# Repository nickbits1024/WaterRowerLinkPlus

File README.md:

# WaterRower Link+

## Description
WaterRower Link+ is a bluetooth module designed for any WaterRower with the S4 monitor.  It provides all the functionality of the official WaterRower ComModule as well as many additional features.

## Features
- Replaces WaterRower ComModule and External ANT+ Module
  - External ANT+ connection Works on M1 when using recommended cable (unlike the official ANT+ Plugin-In module!)
- Bluetooth
  - Bluetooth Fitness Machine Profile
    - Rower Data
    - Indoor Bike Data
  - Supports BLE HRMs
- ANT+
  - Fitness Equipment Profile
  - Supports ANT+ HRMs
- S4 monitor heart rate provider
  - Sends captured ANT+/BLE HR data for display on S4 monitor
- ANT+ to BLE HRM bridge
  - WRL+ will broadcast ANT+ HR data over BLE for use in apps that only support BLE. e.g. SuperNatural

## Tested Software
- WaterRower Connect
- Holofit
- VZFit
- ZWift
- Garmin Fenix 6
- SuperNatural (HR only)

## Hardware
Hardware design is available in the KiCad projects in this repo.  There are two versions, [breadboard](hardware/breadboard/) and [PCB](hardware/pcb/).  With the breadboard version, everything can be assembled using dev boards and jumper wires. [^1]  Both solderless and soldered breadboards were tested and work.  The PCB version requires the design be sent to a PCB manufacturer.

### Soldered Breadboard Version

### PCB Version

## Breadboard Bill of Materials
|Qty|Reference|Part|Foot Print|Supplier|
|---|---------|----|----------|--------|
|1|C1|1uF|THT||[Amazon](https://www.amazon.com/gp/product/B085RDTCCV)
|1|C2|0.1uF|THT||(See above)
|1|J1|AudioPlug3|2.54mm|[Amazon](https://www.amazon.com/gp/product/B07L3P93ZD)
|1|J4|USB_A|2.54mm|[Amazon](https://www.amazon.com/gp/product/B07MBSTZYG)
|2|R1, R2|10k|THT|[Amazon](https://www.amazon.com/gp/product/B072BL2VX1)
|1|SW2|Button|12mm|[Amazon](https://www.amazon.com/gp/product/B07F8GBWGG)
|1|U1|ESP32-S3-DevKitC-1|DIP|[Amazon](https://www.amazon.com/gp/product/B09CPNRDND)
|1|U2|LM3525M-H|SOIC-8|[Mouser](https://www.mouser.com/ProductDetail/926-LM3525MX-H-NOPB)
|1|U2|SOIC-8 TO DIP||[Amazon](https://www.amazon.com/gp/product/B07CJ96ZPW)
|1|U3|D52QD2M6IA[^2]|2x10_2.54mm|[Digi-Key](https://www.digikey.com/en/products/detail/garmin-canada-inc/D52QD2M6IA-A-TRAY/6149453)
|1||PCB Breadboard|50x100|[Amazon](https://www.amazon.com/gp/product/B07ZP4FYVJ)
|1|Project Box|B07W78LN1V|100 x 60 x 25|[Amazon](https://www.amazon.com/gp/product/B07W78LN1V)
|1|TRS Cable|CC0377|3.5mm|[Amazon](https://www.amazon.com/gp/product/B01K3WXQDW)
|1|USB Cable|3896|Mini USB|[Monoprice](https://www.monoprice.com/product?p_id=3896)

## PCB Bill of Materials
|Qty|Reference|Part|Foot Print|Supplier|
|---|---------|----|----------|--------|
|2|C1, C3|1uF cap|0603|[Amazon](https://www.amazon.com/gp/product/B06XDG3WQX)
|8|C2, C4, C5, C6, C9, C10, C14, C16|0.1uF cap|0603|(See above)
|2|C7, C11|C 10uF cap|0603|(See above)
|4|C8, C12, C13, C15|4.7uF cap|0603|(See above)
|1|D1|SK6812|5x5mm|[Digi-Key](https://www.digikey.com/en/products/detail/adafruit-industries-llc/1655/5154679)
|1|D2|1N5819|SOD-323|[Digi-Key](https://www.digikey.com/en/products/detail/micro-commercial-co/B5819WS-TP/2213555)
|1|D3|RED LED|0603|[Amazon](https://www.amazon.com/gp/product/B01CUGA380)
|1|J1|Molex_67643|USB-A|[Mouser](https://www.mouser.com/ProductDetail/538-67643-3910)
|1|J2|CUI_SJ-3523|3.5mm|[Mouser](https://www.mouser.com/ProductDetail/490-SJ-3523-SMT-TR)
|1|J3|Molex-105017-0001|Micro USB|[Mouser](https://www.mouser.com/ProductDetail/538-105017-0001)
|1|Q1|BSS138|SOT-23|[Mouser](https://www.mouser.com/ProductDetail/512-BSS138W)
|2|Q2, Q3|S8050|SOT-23|[Amazon](https://www.amazon.com/gp/product/B07KPCBP24)
|7|R1, R3, R4, R5, R6, R8, R11|10K res|0603|[Amazon](https://www.amazon.com/gp/product/B095P6L5PB)
|2|R2, R7|1K res|0603|(See above)
|1|R9|47K res|0603|(See above)
|1|R10|22K res|0603|(See above)
|1|R12|5.1K res|0603|(See above)
|1|SW2|Header|2x2.54mm|[Amazon](https://www.amazon.com/gp/product/B01461DQ6S) 
|1|SW2|Button|12mm|[Amazon](https://www.amazon.com/gp/product/B07F8GBWGG)
|1|SW4|RESET|2x2.54mm|(See above)
|1|SW1|RESET|6x6mm|[Amazon](https://www.amazon.com/gp/product/B077N3D7BD)
|1|SW3|BOOT|6x6mm|(See RESET)
|1|U1|ESP32-S3-WROOM-1|ESP32-S3-WROOM-1|[Mouser](https://www.mouser.com/ProductDetail/356-ESP32-S3WROOM1N8)
|1|U2|LM3525M-H|SOIC-8|[Mouser](https://www.mouser.com/ProductDetail/926-LM3525MX-H-NOPB)
|1|U3|D52Q|D52QD2M4IA|[Digi-Key](https://www.digikey.com/en/products/detail/garmin-canada-inc/D52QD2M4IA-TRAY/6149451)
|1|U4|CP2102N-Axx-xQFN24|QFN-24|[Digi-Key](https://www.digikey.com/en/products/detail/silicon-labs/CP2102N-A02-GQFN24/9863476)
|1|U5|AP7361C-33E|SOT-223|[Digi-Key](https://www.digikey.com/en/products/detail/diodes-incorporated/AP7361-33E-13/4249788)
|1|U6|SP0506BAATG|MSOP-8|[Mouser](https://www.mouser.com/ProductDetail/576-SP0506BAATG)
|1|Project Box|B07W78LN1V|100 x 60 x 25|[Amazon](https://www.amazon.com/gp/product/B07W78LN1V)
|1|TRS Cable|CC0377|3.5mm|[Amazon](https://www.amazon.com/gp/product/B01K3WXQDW)
|1|USB Cable|3896|Mini USB|[Monoprice](https://www.monoprice.com/product?p_id=3896)
|1|Light Pipe||RA|[Digi-Key](https://www.digikey.com/en/products/detail/dialight/51513620375F/9742144)

## Cable Connections
1. Attach mini USB cable to S4 monitor and WaterRower Link+
2. Attach 3.5mm cable to S4 monitor and WaterRower Link+.  The recommended cable will fit in the narrow gap of an M1 rower and the monitor.
2. Attach micro USB cable to USB power supply

### Required Software
- [Visual Studio Code](https://code.visualstudio.com/download)
- [Visual Studio Code Espressif IDF extension](https://marketplace.visualstudio.com/items?itemName=espressif.esp-idf-extension)
- [ESP-IDF](https://dl.espressif.com/dl/esp-idf/) Built using commit 0132079fa51f2c130513dd634e97ef9726f00e85

### Equipment Used
- Soldering Iron: [YIHUA 995D+](https://www.amazon.com/gp/product/B0919MS875)
- PCB Hot Plate: [MINIWARE MHP30M Mini Hot Plate](https://www.amazon.com/gp/product/B08R6XFPKR)
- PCB Holder: [Stickvise](https://www.stickvise.com/)
- Microscope: [AMScope SM745NTP-B](https://amscope.com/products/sm745ntp-b) + [DAB](https://amscope.com/products/DAB)

## Usage
Once power is provided, a red LED will illuminate on the board and should be detectable in apps.  Press the button connected to SW2 turn on the S4 monitor.  The NeoPixel will illuminate green when it detects it over the USB connection.  It will power off automatically after 30 minutes of inactivity.  When WRL+ is receiving data from the S4, the LED will turn cyan. When it detects a heart rate over BLE or ANT+, it will beat red.
Note the software only supports one HRM.  If multiple are detected, only the first one seen will be connected.

## Known Issues
- The last update to VZfit displays HR in the HUD however the value does not appear correct.  It may be a bug with WRL+ or VZfit.

## Credits
This project was inspired by [PiRowFlow](https://github.com/inonoob/pirowflo)

[^1]: The LM3525M must be soldered to the SOIC-8 TO DIP first
[^2]: This part is EOL at Digi-Key.  I do not know if there is a compatible replacement.

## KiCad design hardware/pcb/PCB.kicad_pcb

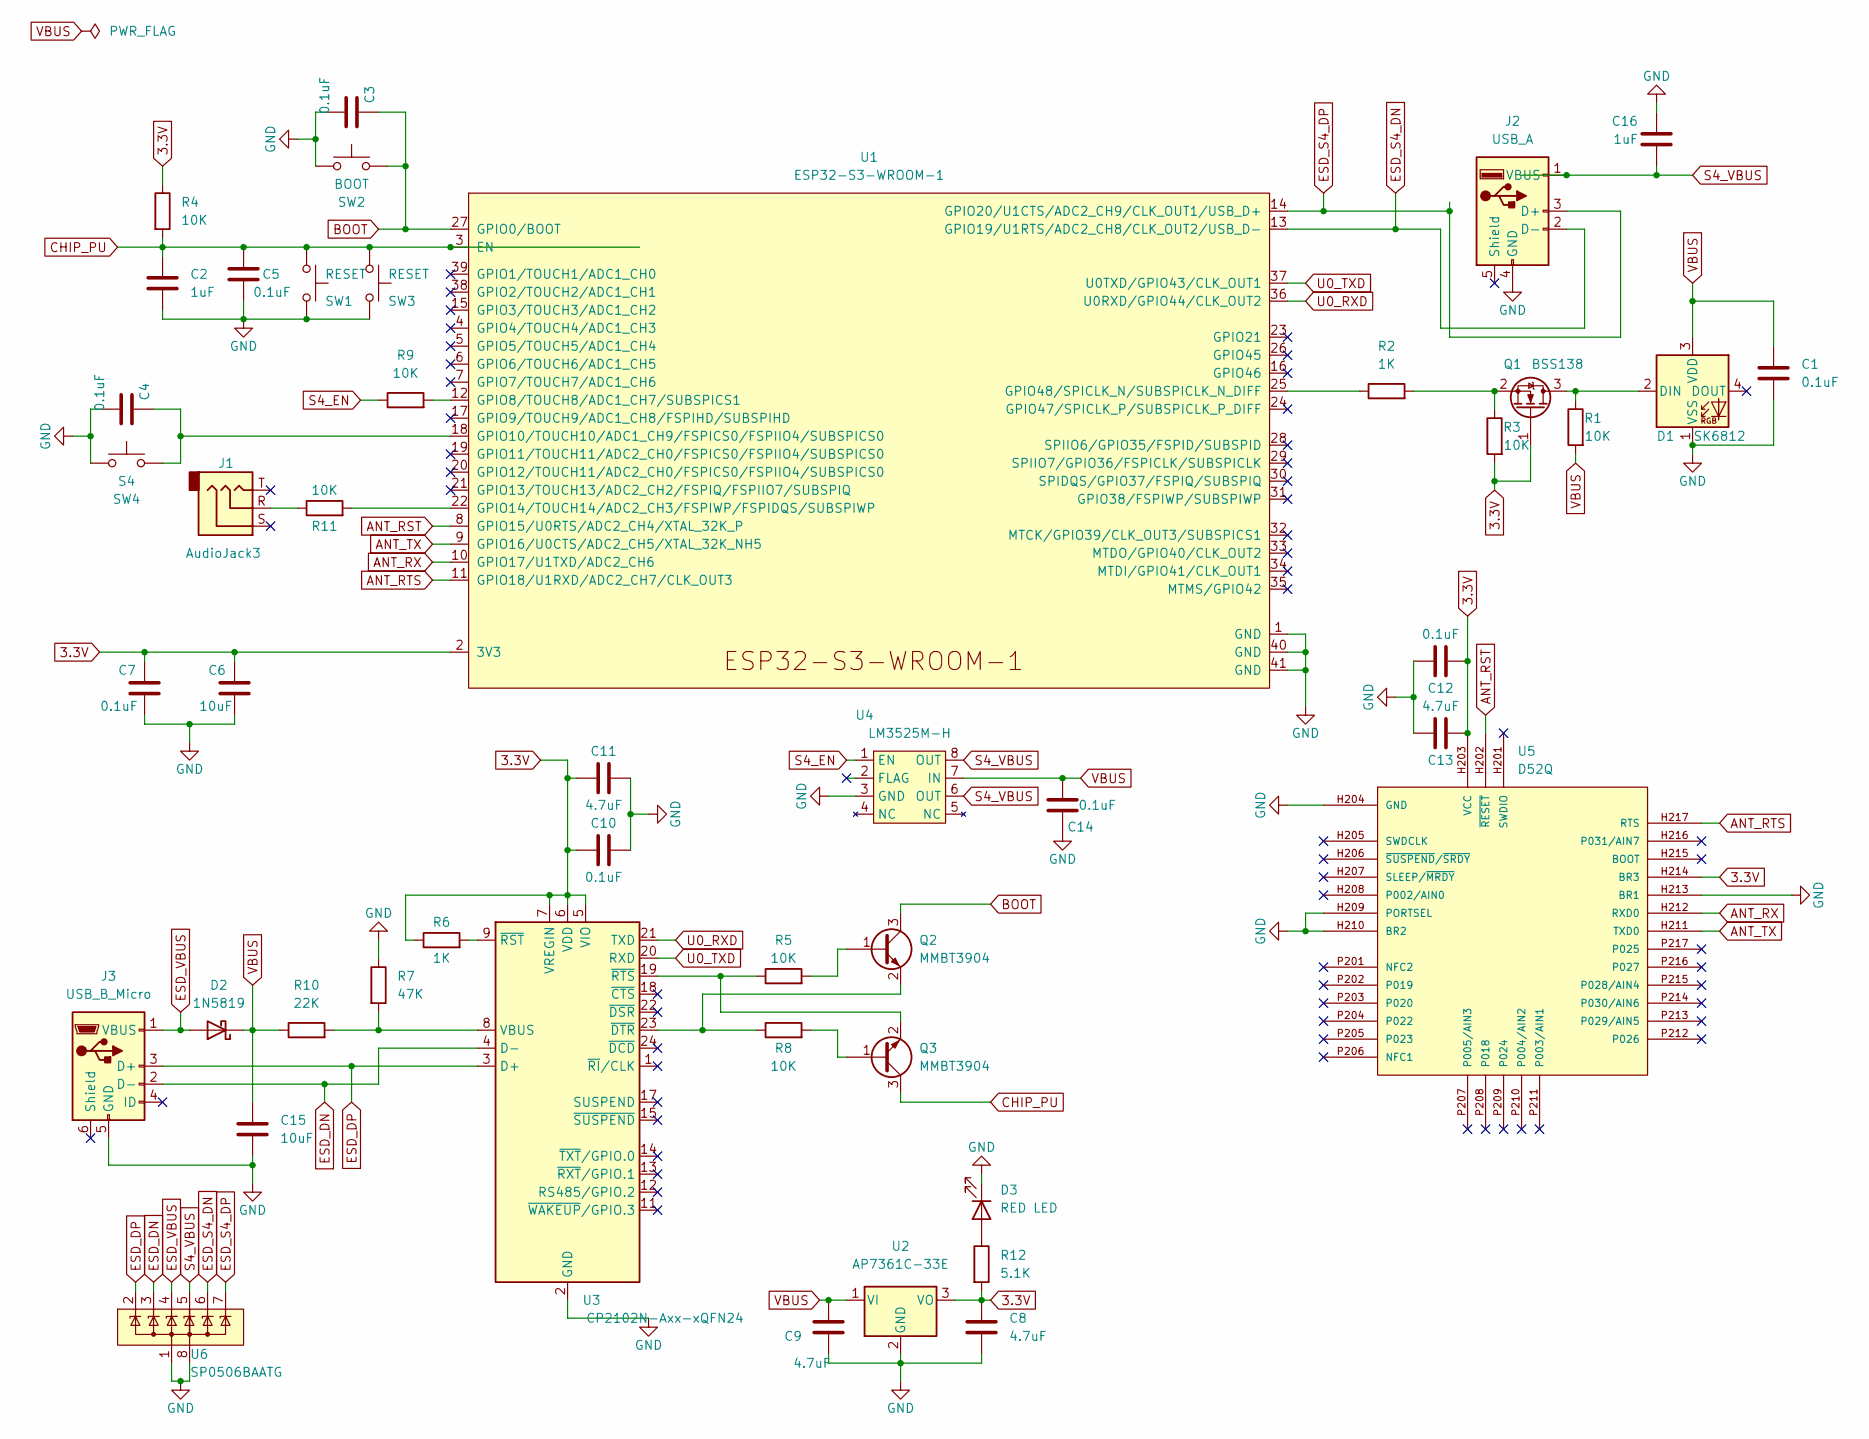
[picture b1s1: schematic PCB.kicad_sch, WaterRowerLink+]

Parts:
C1, C3, C4, C5, C7, C10, C12, C14: 0.1uF; C_0603_1608Metric_Pad1.08x0.95mm_HandSolder
C2, C16: 1uF; C_0603_1608Metric_Pad1.08x0.95mm_HandSolder
C6, C15: 10uF; C_0603_1608Metric_Pad1.08x0.95mm_HandSolder
C8, C9, C11, C13: 4.7uF; C_0603_1608Metric_Pad1.08x0.95mm_HandSolder
D1: SK6812; LED_SK6812_PLCC4_5.0x5.0mm_P3.2mm
D2: 1N5819; D_SOD-323_HandSoldering
D3: RED LED; LED_0603_1608Metric_Pad1.05x0.95mm_HandSolder
J1: AudioJack3; Jack_3.5mm_CUI_SJ-3523-SMT_Horizontal
J2: USB_A; USB_A_Molex_67643_Horizontal
J3: USB_B_Micro; USB_Micro-B_Molex-105017-0001
Q1: BSS138; SOT-23
Q2, Q3: MMBT3904; SOT-23
R1, R3, R4, R5, R8, R9, R11: 10K; R_0603_1608Metric_Pad0.98x0.95mm_HandSolder
R2, R6: 1K; R_0603_1608Metric_Pad0.98x0.95mm_HandSolder
R7: 47K; R_0603_1608Metric_Pad0.98x0.95mm_HandSolder
R10: 22K; R_0603_1608Metric_Pad0.98x0.95mm_HandSolder
R12: 5.1K; R_0603_1608Metric_Pad0.98x0.95mm_HandSolder
SW1: RESET; SW_Push_1P1T_NO_6x6mm_H9.5mm
SW2: BOOT; SW_Push_1P1T_NO_6x6mm_H9.5mm
SW3: RESET; JST_XH_B2B-XH-A_1x02_P2.50mm_Vertical
SW4: S4; JST_XH_B2B-XH-A_1x02_P2.50mm_Vertical
U1: ESP32-S3-WROOM-1
U2: AP7361C-33E; SOT-223
U3: CP2102N-Axx-xQFN24; QFN-24-1EP_4x4mm_P0.5mm_EP2.6x2.6mm
U4: LM3525M-H; SOIC-8_3.9x4.9mm_P1.27mm
U5: D52Q
U6: SP0506BAATG; MSOP-8_3x3mm_P0.65mm

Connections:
3.3V: C6.1, C7.1, C8.2, C10.1, C11.1, C12.1, C13.1, Q1.1 (G), R3.2, R4.1, R6.1, R12.2, U1.2 (3V3), U2.3 (VO), U3.5 (VIO), U3.6 (VDD), U3.7 (VREGIN), U5.H203 (VCC), U5.H214 (BR3)
ANT_RST: U1.8 (GPIO15/U0RTS/ADC2_CH4/XTAL_32K_P), U5.H202 (~RESET)
ANT_RTS: U1.11 (GPIO18/U1RXD/ADC2_CH7/CLK_OUT3), U5.H217 (RTS)
ANT_RX: U1.10 (GPIO17/U1TXD/ADC2_CH6), U5.H212 (RXD0)
ANT_TX: U1.9 (GPIO16/U0CTS/ADC2_CH5/XTAL_32K_NH5), U5.H211 (TXD0)
BOOT: C3.1, Q2.3 (C), SW2.2, U1.27 (GPIO0/BOOT)
CHIP_PU: C2.1, C5.2, Q3.3 (C), R4.2, SW1.2, SW3.2, U1.3 (EN)
ESD_DN: J3.2 (D-), U3.4 (D-), U6.3
ESD_DP: J3.3 (D+), U3.3 (D+), U6.2
ESD_S4_DN: J2.2 (D-), U1.13 (GPIO19/U1RTS/ADC2_CH8/CLK_OUT2/USB_D-), U6.6
ESD_S4_DP: J2.3 (D+), U1.14 (GPIO20/U1CTS/ADC2_CH9/CLK_OUT1/USB_D+), U6.7
ESD_VBUS: D2.2 (A), J3.1 (VBUS), U6.4
GND: C1.1, C2.2, C3.2, C4.2, C5.1, C6.2, C7.2, C8.1, C9.1, C10.2, C11.2, C12.2, C13.2, C14.1, C15.2, C16.1, D1.1 (VSS), D3.1 (K), J2.4 (GND), J3.5 (GND), R7.1, SW1.1, SW2.1, SW3.1, SW4.1, U1.1 (GND), U1.40 (GND), U1.41 (GND), U2.2 (GND), U3.2 (GND), U3.25 (GND), U4.3 (GND), U5.H204 (GND), U5.H209 (PORTSEL), U5.H210 (BR2), U5.H213 (BR1), U6.1, U6.8
unnamed: C4.1, SW4.2, U1.18 (GPIO10/TOUCH10/ADC1_CH9/FSPICS0/FSPIIO4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)
unnamed: D1.2 (DIN), Q1.3 (D), R1.1
unnamed: D3.2 (A), R12.1
unnamed: J1.R, R11.1
unnamed: Q1.2 (S), R2.2, R3.1
unnamed: Q2.1 (B), R5.2
unnamed: Q2.2 (E), R8.1, U3.23 (~DTR)
unnamed: Q3.1 (B), R8.2
unnamed: Q3.2 (E), R5.1, U3.19 (~RTS)
unnamed: R2.1, U1.25 (GPIO48/SPICLK_N/SUBSPICLK_N_DIFF)
unnamed: R9.2, U1.12 (GPIO8/TOUCH8/ADC1_CH7/SUBSPICS1)
unnamed: R11.2, U1.22 (GPIO14/TOUCH14/ADC2_CH3/FSPIWP/FSPIDQS/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)
unnamed: R6.2, U3.9 (~RST)
unnamed: R7.2, R10.2, U3.8 (VBUS)
S4_EN: R9.1, U4.1 (EN)
S4_VBUS: C16.2, J2.1 (VBUS), U4.6 (OUT), U4.8 (OUT), U6.5
U0_RXD: U1.36 (U0RXD/GPIO44/CLK_OUT2), U3.21 (TXD)
U0_TXD: U1.37 (U0TXD/GPIO43/CLK_OUT1), U3.20 (RXD)
VBUS: C1.2, C9.2, C14.2, C15.1, D1.3 (VDD), D2.1 (K), R1.2, R10.1, U2.1 (VI), U4.7 (IN)

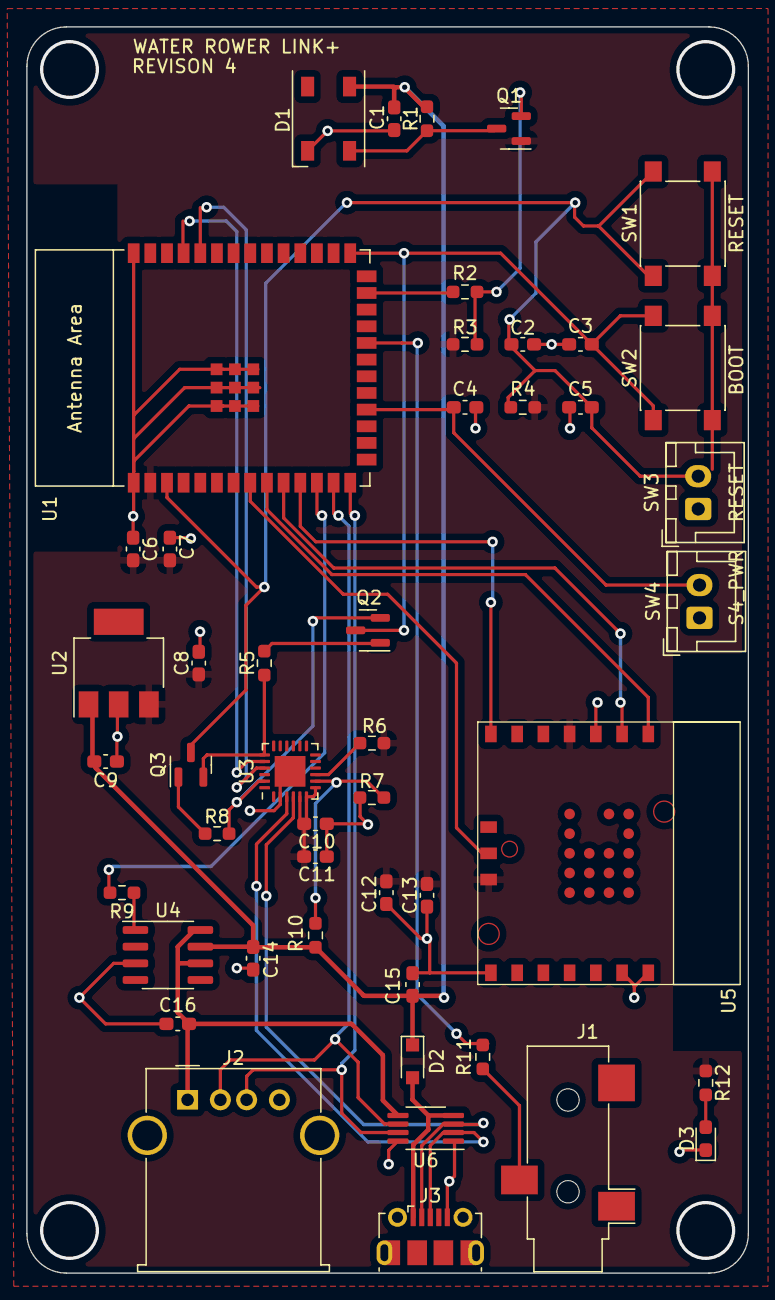
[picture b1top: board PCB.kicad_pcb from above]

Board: 2 copper layers, 55.0 x 95.0 mm, 47 parts (0 on the bottom side), 32 nets.

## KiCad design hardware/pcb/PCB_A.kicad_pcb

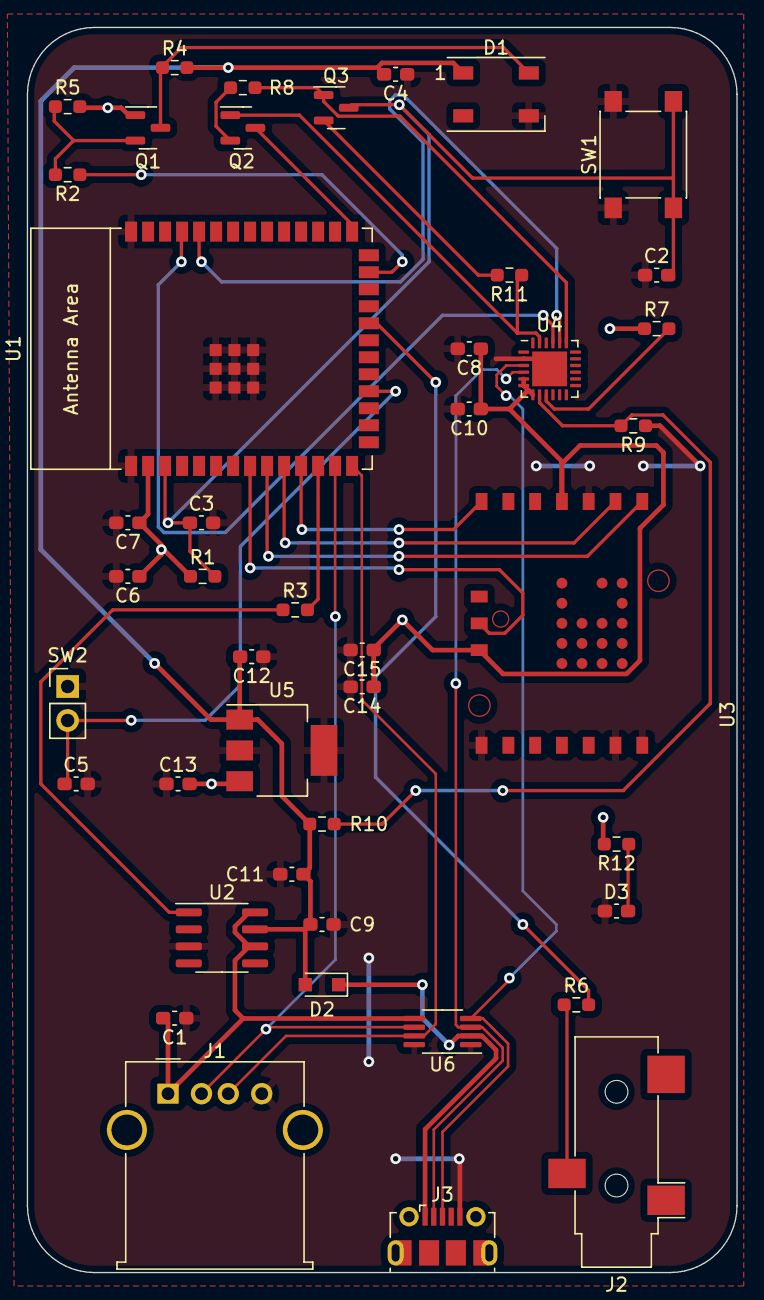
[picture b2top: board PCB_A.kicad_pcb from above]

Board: 2 copper layers, 53.0 x 93.0 mm, 44 parts (0 on the bottom side), 32 nets.

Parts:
C1, C3: 1uF; C_0603_1608Metric_Pad1.08x0.95mm_HandSolder
C2, C4, C5, C6, C9, C10, C14: 0.1uF; C_0603_1608Metric_Pad1.08x0.95mm_HandSolder
C7, C11: 10uF; C_0603_1608Metric_Pad1.08x0.95mm_HandSolder
C8, C12, C13, C15: 4.7uF; C_0603_1608Metric_Pad1.08x0.95mm_HandSolder
D1: WS2812B; LED_WS2812B_PLCC4_5.0x5.0mm_P3.2mm
D2: 1N5819; D_SOD-323_HandSoldering
D3: RED LED; C_0603_1608Metric_Pad1.08x0.95mm_HandSolder
J1: USB_A; USB_A_Molex_67643_Horizontal
J2: AudioJack3; Jack_3.5mm_CUI_SJ-3523-SMT_Horizontal
J3: USB_B_Micro; USB_Micro-B_Molex-105017-0001
Q1: BSS138; SOT-23
Q2, Q3: S8050; SOT-23
R1, R4, R5, R8, R11: 10K; R_0603_1608Metric_Pad0.98x0.95mm_HandSolder
R2, R7: 1K; R_0603_1608Metric_Pad0.98x0.95mm_HandSolder
R3, R6: 10k; R_0603_1608Metric_Pad0.98x0.95mm_HandSolder
R9: 47K; R_0603_1608Metric_Pad0.98x0.95mm_HandSolder
R10: 22K; R_0603_1608Metric_Pad0.98x0.95mm_HandSolder
R12: 4.7K; R_0603_1608Metric_Pad0.98x0.95mm_HandSolder
SW1: SW_RESET; SW_Push_1P1T_NO_6x6mm_H9.5mm
SW2: S4_SW; PinHeader_1x02_P2.54mm_Vertical
U1: ESP32-S3-WROOM-1
U2: LM3525M-H; SOIC-8_3.9x4.9mm_P1.27mm
U3: D52Q
U4: CP2102N-Axx-xQFN24; QFN-24-1EP_4x4mm_P0.5mm_EP2.6x2.6mm
U5: AP7361C-33E; SOT-223-3_TabPin2
U6: SP0506BAATG; MSOP-8_3x3mm_P0.65mm

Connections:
3.3V: C6.1, C7.1, C8.1, C10.1, C13.2, C14.1, C15.1, Q1.1 (G), R1.1, R5.2, R7.1, R12.2, U1.2 (3V3), U3.H203 (VCC), U3.H214 (BR3), U4.5 (VIO), U4.6 (VDD), U4.7 (VREGIN), U5.3 (VO)
ANT_RST: U1.8 (GPIO15/U0RTS/ADC2_CH4/XTAL_32K_P), U3.H202 (~RESET)
ANT_RTS: U1.11 (GPIO18/U1RXD/ADC2_CH7/CLK_OUT3), U3.H217 (RTS)
ANT_RX: U1.10 (GPIO17/U1TXD/ADC2_CH6), U3.H212 (RXD0)
ANT_TX: U1.9 (GPIO16/U0CTS/ADC2_CH5/XTAL_32K_NH5), U3.H211 (TXD0)
BOOT: Q2.3 (C), U1.27 (GPIO0/BOOT)
CHIP_PU: C2.2, C3.1, Q3.3 (C), R1.2, SW1.2, U1.3 (EN)
ESD_DN: J3.2 (D-), U4.4 (D-), U6.3
ESD_DP: J3.3 (D+), U4.3 (D+), U6.4
ESD_S4_DN: J1.2 (D-), U1.13 (GPIO19/U1RTS/ADC2_CH8/CLK_OUT2/USB_D-), U6.6
ESD_S4_DP: J1.3 (D+), U1.14 (GPIO20/U1CTS/ADC2_CH9/CLK_OUT1/USB_D+), U6.7
ESD_VBUS: D2.1 (K), J3.1 (VBUS), U6.2
Earth: C1.1, C2.1, C3.2, C4.1, C5.2, C6.2, C7.2, C8.2, C9.1, C10.2, C11.2, C12.1, C13.1, C14.2, C15.2, D1.3 (VSS), D3.1 (K), J1.4 (GND), J3.5 (GND), R9.1, SW1.1, SW2.1, U1.1 (GND), U1.40 (GND), U1.41 (GND), U2.3 (GND), U3.H204 (GND), U3.H209 (PORTSEL), U3.H210 (BR2), U3.H213 (BR1), U4.2 (GND), U4.25 (GND), U5.2 (GND), U6.1, U6.8
unnamed: C5.1, SW2.2, U1.18 (GPIO10/TOUCH10/ADC1_CH9/FSPICS0/FSPIIO4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)
unnamed: D1.4 (DIN), Q1.3 (D), R4.1
unnamed: D3.2 (A), R12.1
unnamed: J2.R, R6.1
unnamed: Q1.2 (S), R2.2, R5.1
unnamed: Q2.1 (E), R11.1, U4.23 (~DTR)
unnamed: Q2.2 (B), R8.2
unnamed: Q3.1 (E), R8.1, U4.19 (~RTS)
unnamed: Q3.2 (B), R11.2
unnamed: R2.1, U1.25 (GPIO48/SPICLK_N/SUBSPICLK_N_DIFF)
unnamed: R3.2, U1.12 (GPIO8/TOUCH8/ADC1_CH7/SUBSPICS1)
unnamed: R6.2, U1.22 (GPIO14/TOUCH14/ADC2_CH3/FSPIWP/FSPIDQS/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)
unnamed: R7.2, U4.9 (~RST)
unnamed: R9.2, R10.2, U4.8 (VBUS)
S4_EN: R3.1, U2.1 (EN)
S4_VBUS: C1.2, J1.1 (VBUS), U2.6 (OUT), U2.8 (OUT), U6.5
U0_RXD: U1.36 (U0RXD/GPIO44/CLK_OUT2), U4.20 (RXD)
U0_TXD: U1.37 (U0TXD/GPIO43/CLK_OUT1), U4.21 (TXD)
VBUS: C4.2, C9.2, C11.1, C12.2, D1.1 (VDD), D2.2 (A), R4.2, R10.1, U2.7 (IN), U5.1 (VI)

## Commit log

2022-05-07 first
2022-05-07 hr + csc
2022-05-07 ftms
2022-05-07 ble services working
2022-05-07 usb + bt
2022-05-07 ESP32-S3
2022-05-07 usb io
2022-05-07 power button!
2022-05-07 ant+
2022-05-07 power tweak
2022-05-07 S4 HR + hr tweaks
2022-05-07 var tweaks
2022-05-07 spm to zero when stopped
2022-05-07 disable some logging
2022-05-07 reorg
2022-05-07 ble hr
2022-05-07 ble bug fixes clean up
2022-05-07 s4 off tweaks
2022-05-07 cleanup & fix monitor usb reset error
2022-05-07 prototype schematic
2022-05-07 led tweaks
2022-05-07 device unplug robustness
2022-05-07 led status
2022-05-07 ordered pcb
2022-05-07 swap led part#
2022-05-07 tweaks
2022-05-07 pcb tweaks
2022-05-07 board updates
2022-05-07 R3 PCB
2022-05-07 sync pcb GPIO reboot on crash more error handling
2022-05-07 Revision 2: Fixed auto program transistor pins Fixed TX/RX to U0 Increased board size Added screw holes Added BOOT switch Added RESET jumper
2022-05-07 moved CP210N via
2022-05-07 docs WIP
2022-05-07 docs
2022-05-07 required software
2022-05-19 Rev 3: increase screw hole size
2022-06-09 R4 screw hole clearance
2022-06-11 Earth to GND
2022-07-16 add GND via
2022-07-19 remove printf
2022-08-16 small tweaks
2022-08-31 case
2022-08-31 fix 3d models
2022-08-31 grid origin
2022-08-31 case R1
2022-09-02 final case
2022-10-28 config
2023-01-02 update docs
2025-02-07 update idf sdk compatibility
